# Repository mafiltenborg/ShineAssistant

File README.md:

<!-- boardrepo-badge:v1 -->

<!-- /boardrepo-badge:v1 -->

# ShineAssistant (hardware + firmware)
Your way to solar inverter production data without the cloud-stuff!

## Audience
Owners of Growatt 1-3000-s solar inverters who want to integrate to Home Assistant or other local monitoring solutions, rather than relying on Growatt's cloud services.

## Function
This device extracts loads of runtime data from the growatt inverters' modbus-interface and makes it available in several ways; I'll be focusing on the MQTT-approach, but there's also a simple UI, http JSON and a 'Prometheus Scrape Endpoint' to work with as well as some debug data.
* <http://your-ip> is the UI; Runtime data, setup incl. MQTT and firmware update are here.
* <http://your-ip/status> holds JSON formatted data.
* <http://your-ip/metrics> holds the Prometheus formatted data.
* <http://your-ip/debug> offers connection/state debug info to help you get things going.

## What you get
Insight into the life of your solar energy solution. What, how much, when and possibly also a little bit of the 'why'. 
Knowledge is power!  So you get power. It's on you to use it wisely.

## How you get it
### Build the hardware
This is the place for the hardware. Schematics, BOM and all the usual stuff is there for you to poke at. I use KiCAD, and PCBs can be ordered from the gerbers it produces. <https://jlcpcb.com> will readily produce and send the nicest boards at reasonable prices.
### Compile the firmware
Have a look at <https://github.com/mafiltenborg/openinvertergatewaySA> where the fully customized firmware matching the hardware you find here is located. This is not my invention; other smart people have done the heavy lifting, and all I did was tweak and adapt. Still, you'll have to setup camp with PlatformIO and jump through a number of hoops to get at the firmware.
### Print the case
I use OpenSCAD. Luckily, it's free for all, so get cracking and produce .stl-files for your own slicer. You'll likely have to tweak things a bit, as all printers are a little unique.
### And finally
Setup your data extraction scheme as you see fit.

No, I won't sell you a ready made device. I also won't come around and install it. This is DIY, and for obvious reasons DIY-as-a-Service (DIYaaS) does not exist.

## How you use it
That's entirely up to you. Over time, I'll show a couple of examples here, hoping to inspire punters. But like with everything else in this project, it's up to you to assemble the 'virtual LEGO blocks' your own way.

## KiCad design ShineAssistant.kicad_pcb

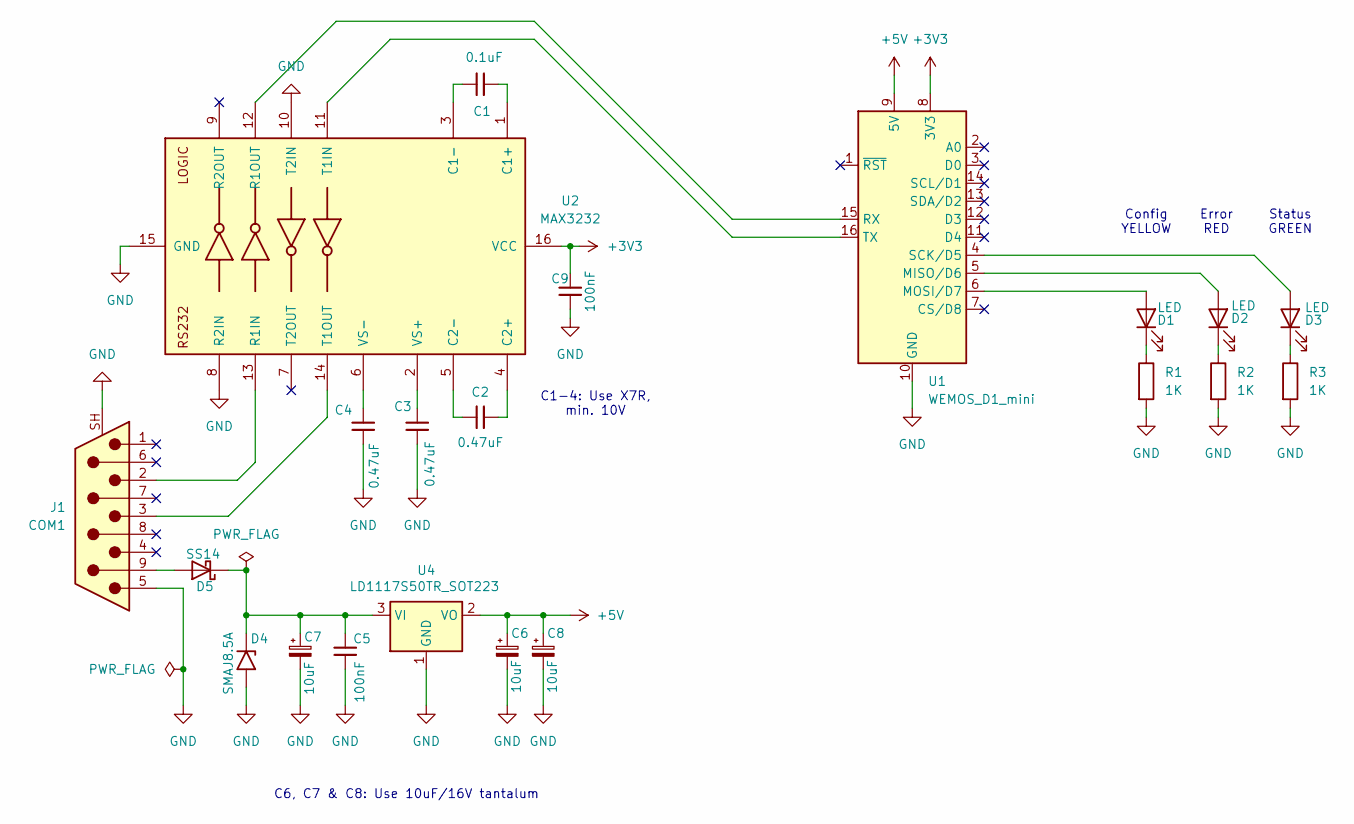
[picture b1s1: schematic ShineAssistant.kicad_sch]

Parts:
C1: 0.1uF; C_0805_2012Metric_Pad1.18x1.45mm_HandSolder
C2, C3, C4: 0.47uF; C_0805_2012Metric_Pad1.18x1.45mm_HandSolder
C5, C9: 100nF; C_0805_2012Metric_Pad1.18x1.45mm_HandSolder
C6, C7, C8: 10uF; C_1206_3216Metric_Pad1.33x1.80mm_HandSolder
D1, D2, D3: LED; LED_0805_2012Metric_Pad1.15x1.40mm_HandSolder
D4: SMAJ8.5A; D_SMA
D5: SS14; D_SMA
J1: COM1; DSUB-9_Pins_Horizontal_P2.77x2.84mm_EdgePinOffset7.70mm_Hou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
R1, R2, R3: 1K; R_0805_2012Metric_Pad1.20x1.40mm_HandSolder
U1: WEMOS_D1_mini; WEMOS_D1_mini_light
U2: MAX3232; TSSOP-16_4.4x5mm_P0.65mm
U4: LD1117S50TR_SOT223; SOT-223-3_TabPin2

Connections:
+3V3: C9.1, U1.8 (3V3), U2.16 (VCC)
+5V: C6.1, C8.1, U1.9 (5V), U4.2 (VO)
GND: C3.2, C4.1, C5.2, C6.2, C7.2, C8.2, C9.2, D4.2 (A2), J1.5, J1.SH (PAD), R1.2, R2.2, R3.2, U1.10 (GND), U2.8 (R2IN), U2.10 (T2IN), U2.15 (GND), U4.1 (GND)
unnamed: D1.2 (A), U1.6 (MOSI/D7)
unnamed: D1.1 (K), R1.1
unnamed: D2.2 (A), U1.5 (MISO/D6)
unnamed: D2.1 (K), R2.1
unnamed: D3.2 (A), U1.4 (SCK/D5)
unnamed: D3.1 (K), R3.1
unnamed: C5.1, C7.1, D4.1 (A1), D5.1 (K), U4.3 (VI)
unnamed: D5.2 (A), J1.9
unnamed: U1.15 (RX), U2.12 (R1OUT)
unnamed: U1.16 (TX), U2.11 (T1IN)
unnamed: C1.1, U2.1 (C1+)
unnamed: C1.2, U2.3 (C1-)
unnamed: C2.1, U2.4 (C2+)
unnamed: C2.2, U2.5 (C2-)
unnamed: J1.2, U2.13 (R1IN)
unnamed: J1.3, U2.14 (T1OUT)
unnamed: C3.1, U2.2 (VS+)
unnamed: C4.2, U2.6 (VS-)

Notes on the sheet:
Config YELLOW
C1-4: Use X7R, min. 10V
Error RED
Status GREEN
C6, C7 & C8: Use 10uF/16V tantalum

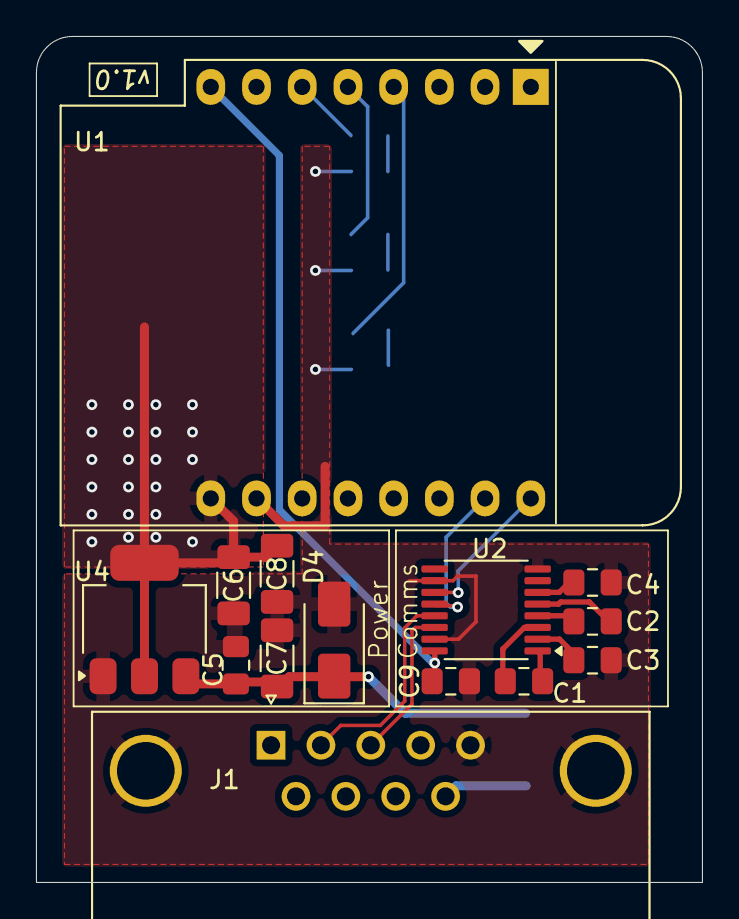
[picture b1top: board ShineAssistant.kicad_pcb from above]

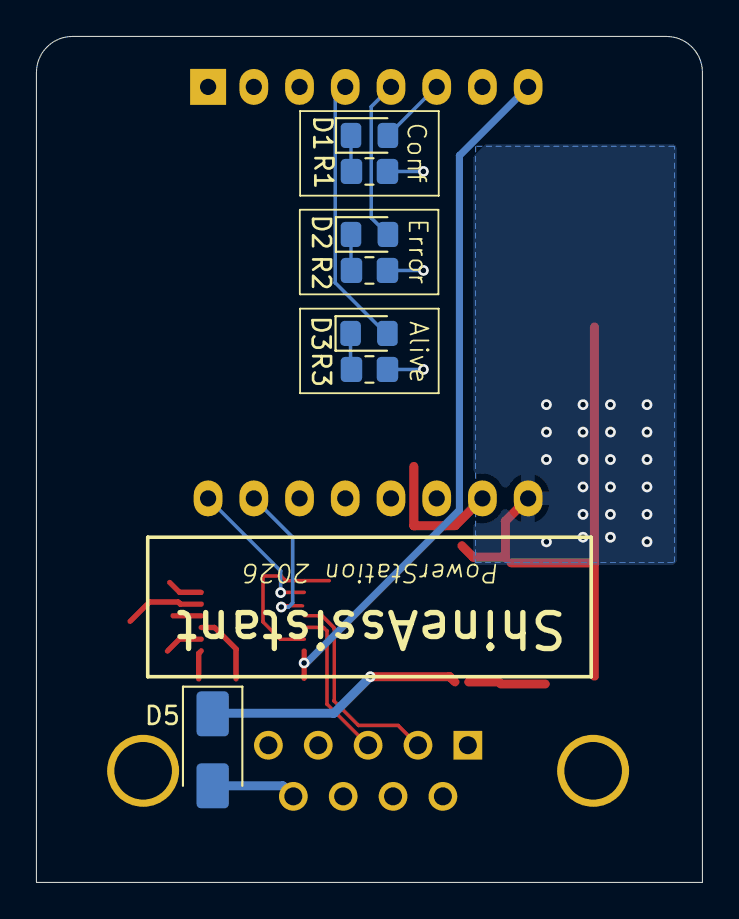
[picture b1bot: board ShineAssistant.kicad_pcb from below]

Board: 2 copper layers, 37.0 x 47.0 mm, 21 parts (7 on the bottom side), 21 nets.
